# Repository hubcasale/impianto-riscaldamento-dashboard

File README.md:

# Impianto riscaldamento dashboard

Due schede Lovelace per Home Assistant, pensate per un impianto con **boiler solare**, **puffer** e
**caldaia a pellet Micronova (Nobis Polygon)** letta dall'integrazione
[`aguaiot_hubcasale`](https://github.com/hubcasale/home_assistant_micronova_agua_iot_hubcasale):

| Scheda | Cosa fa |
|---|---|
| `impianto-overview-card` | Il boiler solare con temperatura alta e bassa, acqua in uscita e docce stimate; il puffer; la caldaia con fiamma piccola (accensione) o grande (in lavoro), stato, temperature, pressioni, contatori del giorno e le richieste del sistema di suggerimento. |
| `caldaia-schedule-card` | La programmazione settimanale della caldaia: 4 programmi con orari, giorni e set di temperatura, **vista settimanale a barre**, **avviso di sovrapposizione** e **preset** (feriale, weekend, vacanza…) con un tocco. |

Funzionano sia su tema chiaro che scuro (usano i colori del tema di Home Assistant) e si adattano al telefono.

> Gli screenshot vengono dal banco di prova (`dev/index.html`) con dati di esempio.
> Il lunedì P1 e P3 si sovrappongono apposta, per mostrare l'avviso.

## Puffer senza Internet

La temperatura del puffer arriva dal cloud Micronova e senza Internet diventa non disponibile. `sensor.puffer_temperatura_effettiva` (in `ha-packages/caldaia_integrazione_blocco.yaml`) usa la lettura della caldaia finché c'è; se manca da più di 5 minuti la ricava dalla sonda ESP32 in ingresso alla serpentina di integrazione con il modello `puffer = T_amb + (sonda − T_amb) / k` (k = 0,753 e T_amb = 19,7 °C, ricavati il 8/10/2026 da 747 letture a pompa in marcia: errore medio 0,8 °C). La sonda legge il puffer solo con la pompa in marcia: a pompa ferma il valore non è affidabile e la regola di blocco/forzatura **non interviene mai**. Sulla scheda il puffer compare con la scritta «stima sonda». Parametri regolabili: minuti di attesa, k e temperatura ambiente.

## Pannello solare sulla scheda

Sotto il puffer da 50 litri la scheda disegna la sagoma del pannello solare, collegata alla serpentina solare del boiler. Il colore segue la temperatura (come il boiler, poi più scuro oltre i 65 °C).
- **Temperatura mostrata:** la stima del collettore (`sensor.solare_termico_t_collettore_stimata`), ritarata sulle letture reali del display del regolatore e valida sia a pompa ferma sia in marcia. La temperatura **misurata** in ingresso alla serpentina (`sensor.solare_termico_solare_serpentina_ingresso`) è il fluido dopo i tubi, circa 6-7 °C sotto il collettore: compare sui tubi, e diventa il valore del pannello solo se la stima manca.
- **Sui tubi** compaiono le temperature in ingresso e in uscita della serpentina solare; nel disegno del CLESS le sonde dei pozzetti (b di destra = S. BOILER della caldaia, c di destra = generatore, b di sinistra = minima per il riscaldamento, sonde ESP32 `..._puffer_generatore` e `..._puffer_minima_riscaldamento`).
- **Massima prevista del giorno** e **massima già raggiunta oggi**: `ha-packages/solare_pannello.yaml`. Il modello usa la previsione oraria di `weather.casale` (nuvolosità, temperatura, umidità), la posizione del sole, l'inclinazione e l'orientamento dei collettori, il modello del collettore già in uso e, nelle prime ore, l'**irraggiamento misurato adesso** (rapporto fra irraggiamento sul piano e cielo sereno, con peso che scende in circa 2 ore). La massima prevista non scende mai sotto quella già raggiunta. È una stima del collettore a pompa ferma: con la pompa in marcia il fluido misurato resta più freddo.
- Entità nuove: `sensor.solare_pannello_temperatura`, `sensor.solare_pannello_massima_prevista`, `sensor.solare_pannello_massima_oggi`, `sensor.solare_previsione_oraria`. Il fattore `input_number.solare_pannello_fattore_sereno` (1,00) calibra l'irraggiamento a cielo sereno.
- **Telefono:** sotto il boiler compare una fascia con il puffer e il pannello, con le scritte più grandi (le temperature in ingresso e in uscita delle serpentine sono indicate con le frecce → e ←). Sulla scheda larga i tubi riportano solo le temperature; la tessera «Solare» a sinistra mostra i kW.

## Stima del consumo di pellet

`ha-packages/caldaia_pellet.yaml` stima i chili di pellet bruciati e la scheda li mostra sotto i contatori di oggi (oggi, settimana, mese). È una **stima** da calibrare: la caldaia non comunica i chili. Il modello usa lo stato e la potenza reale:
- **WORK:** consumo interpolato fra i due valori del costruttore (1,63 kg/h al 30 %, 5,6 kg/h al 100 %) in base alla potenza reale (30 % al minimo, 100 % al massimo);
- **STAND BY e STOP:** consumo di mantenimento (0,2 kg/h, ipotesi);
- **ogni accensione** (ingresso in START): 200 g (ipotesi);
- ECO STOP, OFF e WAIT: nessun consumo.

Per tarare: dividi i chili di pellet realmente consumati in un periodo (sacchi aperti e finiti) per la stima dello stesso periodo e inserisci il risultato come fattore di taratura nelle preferenze (sezione «Consumo di pellet», ripiegata). Entità: `sensor.caldaia_pellet_oggi`, `_settimana`, `_mese` (si azzerano da sole), `sensor.caldaia_pellet_stimato_totale`, `sensor.caldaia_pellet_consumo_istantaneo` (kg/h).

Sui dati dal 2 al 6 ottobre 2026 il modello dà circa 2-6 kg al giorno, con poche ore in lavoro e molte accensioni.

## Preferenze dalla scheda dell'impianto

Il pulsante a forma di ingranaggio in alto a destra sulla scheda dell'impianto apre le preferenze, divise in **blocchi per funzione**: *Caldaia a pellet* (temperatura dell'acqua e set boiler), *Accumulo CLESS* e *Gestione dall'accumulo*, *Spegnimento se nessuno è in casa*, *Termostato ambiente* (si apre la finestra dell'integrazione `termostato_riscaldamento`, se è installata) e, sotto «Avanzate», *Consumo di pellet (stima)* e *Misura delle pompe*. Toccando un blocco si aprono le sue impostazioni; la **«i»** accanto a un blocco o a una voce apre una spiegazione con cosa fa, quando serve e, dove c'è, il valore consigliato (niente suggerimenti al passaggio del mouse: pensato per il tablet). Ogni modifica è attiva subito e resta anche dopo un riavvio. Le impostazioni i cui helper non esistono (pacchetto non installato) non compaiono. Per nascondere il pulsante: `settings: false` nella configurazione della scheda.

## Installazione

### HACS (repository personalizzato)

1. HACS → menu a tre punti → **Repository personalizzati** → incolla
   `https://github.com/hubcasale/impianto-riscaldamento-dashboard`, categoria **Dashboard**.
2. Installa **Impianto riscaldamento dashboard**.
3. Aggiungi le schede a una dashboard (vedi `examples/dashboard.yaml`).

### A mano

1. Copia `dist/impianto-riscaldamento-dashboard.js` in `<config>/www/`.
2. Impostazioni → Dashboard → Risorse → aggiungi `/local/impianto-riscaldamento-dashboard.js` come **Modulo JavaScript**.
3. Ricarica la dashboard.

## `impianto-overview-card`

```yaml
type: custom:impianto-overview-card
title: Impianto acqua calda      # facoltativo
```

Senza altro usa questi nomi di entità (cambiali in `entities:` se i tuoi sono diversi):

| Chiave | Entità predefinita | Da dove viene |
|---|---|---|
| `boiler_top` | `sensor.boiler_solare_alto_stimato` | `ha-packages/boiler_solare.yaml` |
| `boiler_bottom` | `sensor.boiler_solare_basso_stimato` | idem |
| `outlet` | *(assente: si usa la sonda alta)* | temperatura dell'acqua in uscita, se la misuri |
| `cless_mode` | `input_boolean.impianto_modo_cless` | pacchetto `impianto_cless` (vedi «Modo CLESS») |
| `solar_power`, `collector_temp` | `sensor.solare_termico_potenza`, `sensor.solare_termico_t_collettore_stimata` | pacchetto solare termico |
| `puffer`, `stove_state`, `stove_water`, `smoke`, `flame`, `power`, `water_pressure`, `brazier_pressure`, `extractor`, `pump`, `alarm` | `sensor.casale_*` | integrazione `aguaiot_hubcasale` |
| `set_boiler`, `set_water` | `number.casale_setpoint_boiler`, `climate.casale_acqua` (attributo `temperature`) | integrazione |
| `pellet_reserve`, `pellet_empty`, `pellet_open` | `binary_sensor.casale_riserva_legna` (riserva: sta per finire), `binary_sensor.casale_pellet_empty` (vuoto), `binary_sensor.casale_pellet_hopper_open` (serbatoio aperto) | integrazione `aguaiot_hubcasale` v1.2.7-hubcasale.4 (gli ultimi due) |
| `integration_pump`, `collector_pump` | `binary_sensor.caldaia_pompa_integrazione_attiva`, `binary_sensor.caldaia_pompa_collettore_attiva` | `ha-packages/caldaia_pompe_centralina.yaml` (dalla potenza della centralina solare) |
| `integration_power`, `collector_power` | `sensor.garage_bs_pompa_integrazione_potenza` (Shelly 1PM), `sensor.garage_centralina_solare_pompe_potenza` (Shelly EM Mini sull'alimentazione dell'Elios) | i watt accanto alle pompe in marcia |
| `integration_call`, `integration_block_enabled`, `integration_block_wanted` | `binary_sensor.garage_bs_pompa_integrazione_ingresso_0`, `input_boolean.caldaia_integrazione_blocco_attivo`, `binary_sensor.caldaia_integrazione_inutile` | `ha-packages/caldaia_integrazione_blocco.yaml`: la scritta arancione «integrazione bloccata» compare quando il blocco è acceso, la regola lo chiede e l'Elios chiama la pompa |
| `starts_today`, `starts_yesterday`, `standby_today`, `work_hours_today` | `sensor.caldaia_*` | `ha-packages/caldaia_suggerimento.yaml` |
| `request_acs`, `request_heating`, `consent` | `binary_sensor.caldaia_richiesta_acs` … | idem |

Il numero di **docce** si calcola con un modello a due zone: la parte alta del serbatoio (quota `top_share`)
è alla temperatura della sonda alta, il resto a quella della sonda bassa; ogni zona sopra la temperatura
della doccia dà `litri × (T − T_rete) / (T_doccia − T_rete)`. Parametri (numero o id di entità):

```yaml
model:
  volume: 190          # litri utili (predefinito: input_number.boiler_solare_volume)
  top_share: 50        # % di volume della zona alta (predefinito: input_number.boiler_solare_peso_alto)
  mains_temp: 15       # °C acqua di rete (predefinito: input_number.boiler_solare_t_rete)
  shower_volume: 40    # litri per doccia
  shower_temp: 38      # °C della doccia
```

Sotto i 560 px di larghezza il disegno del boiler perde il puffer (resta nelle tessere) per restare leggibile.

**Termostato ambiente sotto la caldaia** (`thermostat: false | { entry_id, title }`): se è installata l'integrazione [termostato-riscaldamento](https://github.com/hubcasale/termostato-riscaldamento) la scheda mostra sotto la caldaia il quadrante con la temperatura, l'obiettivo con + e − e le modalità Programma, Manuale, Timer e Spento. Senza l'integrazione non compare niente. Per nasconderlo: `thermostat: false`. La colonna della caldaia mostra quattro valori (puffer, set boiler, set acqua, potenza), i contatori di oggi e le tre richieste (l'interruttore «Evita partenze inutili» sta nelle preferenze, blocco «Salvaguardia accensioni»); fumi, fiamma, pressioni, estrattore, circolatore, accensioni di ieri, allarme e stima del pellet stanno nella finestra **«Altri dati»**; un allarme in corso resta sempre visibile sulla scheda.

**Layout «split» e pellet nel serbatoio (prova)** (`layout: split`, predefinito `classic`): su schermo largo (oltre 1150 px) boiler, caldaia e stufa a pellet stanno in **tre schede alte uguali**, con lo stesso sfondo, bordo e angoli, e il **termostato** occupa la striscia in basso su tre colonne (quadrante | obiettivo e modalita' | stato, calendario e preferenze). Il boiler e' corto (un solo giro per serpentina). Con `stufa: true` e la scheda `stufa-pellet-card` caricata la stufa e' la scheda completa incorporata (senza la scheda resta la sintesi con il pulsante «Scheda completa»). Sotto i 1150 px le schede si impilano (boiler, caldaia, stufa, termostato). La figura della caldaia ha **a sinistra l'armadio del serbatoio** con il disegno del serbatoio (stessa forma di quello vero: parte alta, trapezio e punta) riempito fino ai chili rimasti, con i chili, i giorni di autonomia e lo stato del pellet nella parte libera a destra del serbatoio, e **a destra il corpo della caldaia** con la finestra della fiamma, in alto l'ultimo cambio di stato e in basso lo stato (OFF, WORK, ECO STOP...) e la temperatura dell'acqua. Toccando il serbatoio si apre la finestra **«Pellet nel serbatoio»**: con **«Ho versato dei sacchi»** si aggiungono i sacchi (passo di mezzo sacco) e con **«Ho misurato il livello»** si scrive la quota dalla sommita' in cm. Con **«Ho versato dei sacchi e misurato la quota»** si danno insieme i sacchi, la quota di prima (facoltativa) e quella dopo: imposta il livello dalla quota dopo e mostra l'aumento in chili accanto a sacchi x peso, con la densita' che la geometria richiederebbe (solo se la quota di prima e' misurata), per controllare le misure del serbatoio. Il conteggio e' un riferimento (chili e totale stimato di quel momento) meno il consumo stimato da allora: serve il pacchetto `ha-packages/caldaia_pellet_serbatoio.yaml` (helper `caldaia_pellet_kg_riferimento`, `caldaia_pellet_totale_riferimento`, `caldaia_pellet_sacco_kg`; la prima volta si parte dal livello misurato). Il serbatoio tiene 8 sacchi da 15 kg (120 kg), 2,0 kg per cm nella parte alta; la forma e la tabella sono in `src/hopper-logic.ts`.

**Grafici del pellet** (pulsante «Grafici» in alto a destra del serbatoio): finestra con il periodo a scelta (24 ore, 3, 7, 14, 30 o 90 giorni), le caselle riassuntive (rimasti adesso, consumo medio, consumati e caricati nel periodo, quando finisce), il grafico dei **chili rimasti** con i **caricamenti** (freccia verde, «+15 kg») e le **letture del livello** (punto blu, con lo **scarto** rispetto alla stima in arancione) che si possono accendere e spegnere, il **consumo stimato per giorno** (per ora nel periodo di 24 ore) con la media e, sotto, l'elenco di caricamenti e letture con la **taratura** suggerita per il fattore (consumo reale / stimato). Toccando il grafico si legge il valore in quel momento. I caricamenti e le letture non sono registrati a parte: si riconoscono dai salti del conteggio (il rimasto cala esattamente quanto cresce il totale stimato, quello che non quadra è un evento; un salto vicino a un multiplo di mezzo sacco, o che riempie il serbatoio, è un caricamento), quindi appaiono fin dove arriva lo storico di Home Assistant (di solito 10 giorni); prima si vedono un andamento approssimato e il consumo dalle statistiche a lungo termine. Servono i sensori `sensor.caldaia_pellet_serbatoio` e `sensor.caldaia_pellet_stimato_totale` (pacchetti `caldaia_pellet_serbatoio.yaml` e `caldaia_pellet.yaml`).

**Cosa mostrare (una sola scheda per tutto l'impianto)**: nelle preferenze, blocco **«Pagina → Cosa mostrare»**, quattro interruttori accendono o spengono le sezioni **Boiler solare**, **Caldaia a pellet**, **Stufa a pellet** e **Termostato ambiente**: puoi vederne una sola o tutte. La scelta è **per utente** e resta salvata in Home Assistant (`frontend/set_user_data`, chiave `impianto_riscaldamento_sezioni`), quindi la ritrovi su tutti i tuoi dispositivi; l'ultima sezione rimasta non si può spegnere. Le colonne si adattano alle schede visibili (nel layout classic il boiler lascia tutta la larghezza alle altre). Se la caldaia è nascosta, l'ingranaggio delle preferenze passa in una barra in alto a destra. Gli interruttori compaiono solo per le sezioni disponibili (la stufa serve `stufa: true`, il termostato non dev'essere `thermostat: false`). Per cambiare la scelta di partenza (chi non l'ha mai fatta) c'è `show: [boiler, caldaia, stufa, termostato]` nella configurazione YAML.

**Colore della scheda** (`color`, dall'editor: «Colore della scheda»): lo sfondo della scheda prende una tinta del colore scelto e il bordo lo segue, come un blocco colorato della plancia; i pannelli interni (boiler, caldaia, stufa, termostato, stanze) restano come li disegna il tema. Vale un nome della tavolozza di Home Assistant (`deep-orange`, `blue`, `amber`…) oppure, nello YAML, un colore CSS (`#ff5722`). Senza `color` la scheda resta com'è.

**Preferenze dell'impianto**: l'ingranaggio sta nel titolo della scheda della caldaia, accanto a «Programma» (`settings: false` lo toglie).

**Programmazione della caldaia** (`schedule: false | { prefix, master, status, presets }`, predefinito attivo): nel titolo della scheda della Polygon c'è il pulsante **«Programma»**, che apre in un popup la scheda della programmazione settimanale (`caldaia-schedule-card`) senza passare da altri pop-up o pulsanti della dashboard. Un oggetto passa le opzioni alla scheda della programmazione; `schedule: false` toglie il pulsante.

**Sintesi della stufa a pellet (prova)** (`stufa: true | { entry_id, title }`, predefinito spenta): se è installata l'integrazione [stufa-pellet-monitor](https://github.com/hubcasale/stufa-pellet-monitor), a destra della scheda della caldaia compare una sintesi della stufa: stato e da quanto dura, modo (programma, manuale, timer), potenza, il pulsante di **accensione manuale** dell'interruttore (apre una finestra di conferma) e **«Scheda completa»**, che apre in un popup la scheda `stufa-pellet-card`, aggiornata in tempo reale. Il termostato resta intero sotto. Quando la scheda è più stretta di 1150 px (portatili piccoli, tablet in verticale, telefoni) la sintesi va sotto la caldaia, a tutta larghezza. Senza l'integrazione, o senza `stufa`, non cambia niente.

## `caldaia-schedule-card`

```yaml
type: custom:caldaia-schedule-card
title: Programmazione caldaia     # facoltativo
prefix: casale                    # prefisso delle entità dell'integrazione
hide: [weekly]                    # facoltativo: nasconde "weekly" e/o "presets"
```

Usa le entità create dall'integrazione, per ogni programma N da 1 a 4:
`time.casale_crono_pN_accensione`, `time.casale_crono_pN_spegnimento`,
`number.casale_crono_pN_setpoint_boiler`, `number.casale_crono_pN_setpoint_acqua`,
`switch.casale_crono_pN_<giorno>` (lunedi … domenica) e l'interruttore generale
`switch.casale_cronotermostato_settimanale`.

- **Orari a passi di 10 minuti** (come la caldaia). Spegnimento `00:00` = fino a mezzanotte.
- **Sovrapposizioni**: se due programmi attivi si incrociano nello stesso giorno compare un avviso in alto e la
  fascia è tratteggiata in rosso nella vista settimanale. Fasce che si toccano soltanto non contano; un programma
  che scavalca la mezzanotte occupa anche il giorno dopo.
- **Vista settimanale**: una riga per giorno, con la linea dell'ora attuale.
- Le modifiche sono scritte subito. I campi si attenuano finché la caldaia non conferma (passa dal cloud, può
  servire qualche minuto).

### Preset

Quattro preset predefiniti: *Settimana tipo*, *Feriale*, *Weekend*, *Vacanza*. Toccando un preset la scheda
mostra **che cosa cambierebbe** e chiede conferma; applica solo le differenze. Si possono sostituire:

```yaml
presets:
  - name: Mattina e sera
    icon: mdi:weather-sunset
    description: Dalle 5:30 alle 8 e dalle 17 alle 22:30
    crono: true                 # true/false = attiva/disattiva il cronotermostato; assente = non toccarlo
    programs:
      "1": { on: "05:30", off: "08:00", days: [lun, mar, mer, gio, ven, sab, dom], set_boiler: 45, set_water: 65 }
      "2": { on: "17:00", off: "22:30", days: [lun, mar, mer, gio, ven, sab, dom] }
      "3": null                 # null (o days: []) = programma disattivato
      # "4" non elencato = resta com'è
```

I giorni si scrivono in italiano o inglese, corti o lunghi (`lun`, `mon`, `lunedì`…).

#### Salvare i propri preset

Il pulsante **Salva…** accanto ai preset salva la programmazione attuale (orari, giorni e set di temperatura dei quattro programmi, più lo stato del cronotermostato): scegli quale preset sostituire (anche quelli predefiniti) oppure dai un nome a un preset nuovo. Prima di salvare vedi le righe che verranno memorizzate. I preset salvati compaiono insieme agli altri; per quelli predefiniti sostituiti c'è «Ripristina», per quelli nuovi «Elimina». Si salvano nei dati utente di Home Assistant (`frontend/set_user_data`, chiave `impianto_riscaldamento_presets`), quindi restano dopo gli aggiornamenti e valgono su tutti i dispositivi dello stesso utente. Con `presets:` nella configurazione si sostituiscono i predefiniti, e quelli salvati vengono sopra.

## Pacchetti di Home Assistant e ESPHome

Le schede leggono sensori che qui sono forniti come esempio:

- `ha-packages/boiler_solare.yaml`: temperature stimate alta e bassa (con una correzione provvisoria di accoppiamento rispetto alla centralina
  solare, vedi `docs/MEMORIA.md`), media, stratificazione, energia accumulata e acqua calda equivalente.
- `ha-packages/caldaia_suggerimento.yaml`: suggerimento informativo di accendere o no la caldaia, contatori di
  accensioni e ore in lavoro. **Non comanda niente.**
- `ha-packages/caldaia_tempo_acqua.yaml`: misura quanti minuti servono, dopo un'accensione a freddo, per portare il boiler solare
  alla temperatura d'uso e ne fa la media (ultimi 10 campioni, correggibili a mano).
- `ha-packages/caldaia_pompe_centralina.yaml`: dalla potenza totale della centralina solare (`sensor.garage_centralina_solare_pompe_potenza`) ricava quale pompa gira (ferme sotto 15 W, solo collettore fino a 42 W, solo integrazione tra 42 e 65 W, entrambe da 65 W; soglie modificabili, tarate sulle misure del 5/10/2026) e le ore di funzionamento di oggi.
- `ha-packages/caldaia_accensione_rapida.yaml`: pulsante **Avvia caldaia** per quando serve acqua calda e la Polygon è spenta,
  con spegnimento automatico (vedi sotto) e la stima `sensor.caldaia_acqua_pronta_tra`.
- `esphome/solare-termico.yaml`: ESP32 con ADS1115 e sonde NTC 10k B3950 (serpentine) e due sonde sul boiler.

## Stanze: temperatura e umidità

Accanto al termostato la scheda dell'impianto mostra la scheda **Stanze**: una colonna per ogni stanza (altezza e colore secondo la temperatura, umidità sotto), la linea tratteggiata dell'obiettivo del termostato e, in alto, tre chip: la stanza più calda, la più fredda e quelle con umidità da 70 % in su. Nel layout `split` (tablet, scheda larga almeno 1150 px) il termostato occupa metà riga e le stanze l'altra metà; sotto quella larghezza stanno una sotto l'altra. Un tocco su una colonna apre i **Grafici** sul gruppo *Stanze*, con temperatura (scala a sinistra) e umidità (a destra) di quella stanza; gli altri sensori si accendono dai pulsanti sopra il grafico.

- Colori della temperatura: da 22 °C in su arancione, sotto 19 °C azzurro, in mezzo verde. Umidità: da 60 % gialla, da 70 % rossa, sotto 40 % azzurra.
- Le stanze di partenza e i loro sensori MQTT: Soggiorno, Cucina, Camera matrimoniale, Camera Matilde, Camera Camilla, Bagno Blu (`sensor.sensore_<stanza>_temperature` e `..._humidity`) e Bagno Verde, che resta un segnaposto finché non esiste il suo sensore. La scheda compare se almeno uno di questi sensori esiste.
- Con la configurazione YAML si cambiano le stanze, il titolo o il termostato dell'obiettivo; `rooms: false` la nasconde:

```yaml
type: custom:impianto-overview-card
layout: split
rooms:
  title: Stanze
  target_entity: climate.termostato
  rooms:
    - { id: studio, name: Studio, short: Studio, temperature: sensor.studio_temperatura, humidity: sensor.studio_umidita }
```

La scheda si può usare anche da sola: `type: custom:impianto-rooms-card` (opzioni `title`, `rooms`, `target_entity`).

## Modo CLESS

Con l'accumulo REQ.A CLESS al posto del boiler solare da 200 L e del puffer da 50 L si accende `input_boolean.impianto_modo_cless` (pacchetto `ha-packages/impianto_cless.yaml`). Da acceso:

- la scheda disegna l'accumulo senza puffer, senza serpentina e pompa di integrazione e senza il pulsante di accensione rapida; al posto dell'«Acqua pronta in» mostra il setpoint della sonda S. BOILER, e la finestra «Stato» parla della sonda S. BOILER invece del puffer;
- il modello del serbatoio passa a 510 L (zona alta circa il 45 %), le correzioni delle sonde ESP32 vanno a 0 (da rifare confrontando la sonda alta con la S. BOILER) e le docce si contano sopra i 47 °C (la serpentina sanitaria non raffredda l'accumulo oltre quella soglia): con la cima a 65 °C sono circa 4, non 12 come col conto da boiler a serbatoio;
- la salvaguardia delle partenze inutili, il blocco della pompa di integrazione e la misura del tempo per l'acqua pronta si fermano (la caldaia resta sempre accesa per l'acqua calda);
- se la caldaia resta spenta più di 20 minuti (regolabile) senza programma settimanale e con qualcuno in casa arriva un avviso sul telefono; non viene riaccesa da sola.
- la **gestione dall'accumulo** (pacchetto `ha-packages/caldaia_accumulo.yaml`, interruttore `input_boolean.caldaia_accumulo_attivo`) decide le ripartenze dalla sonda S. BOILER invece che dall'acqua della caldaia: se la caldaia riparte da sola da ECO STOP o STAND BY con S. BOILER a 55 °C o più (`input_number.caldaia_accumulo_t_spegni`) e nessuno chiede calore, la partenza si annulla in fase di accensione (anche se il termostato chiede riscaldamento: i radiatori sono serviti dall'accumulo); spenta così, si riaccende quando S. BOILER scende sotto 53 °C (`..._t_accendi`) o quando la caldaia chiede riscaldamento con l'accumulo sotto la soglia di spegnimento. Non tocca le partenze da OFF (a mano, app, accensione rapida), l'accensione rapida in corso e gli allarmi; in questo caso l'avviso di caldaia spenta non scatta.

Nelle Preferenze, col modo CLESS acceso, il blocco **Gestione dall'accumulo** (interruttore e le due soglie) è accanto a quello dell'accumulo; il campo del setpoint della caldaia diventa «Set boiler (sonda S. BOILER)» con una nota sull'isteresi dell'acqua. I blocchi del vecchio impianto (salvaguardia delle accensioni, richiesta di acqua calda, pompa di integrazione) sono stati tolti dalle preferenze: le loro helper e i pacchetti restano in Home Assistant, ma non si comandano più da qui.

L'interruttore, le correzioni delle due sonde, la soglia delle docce e l'avviso di caldaia spenta stanno nelle **Preferenze impianto → Accumulo CLESS** (l'interruttore è nell'intestazione del blocco). Da spento torna tutto com'era (200 L, 50 %, correzioni +4 e +3 °C). Senza il pacchetto, o con il modo spento, la scheda non cambia.

## Pulsante «Stato»

Sotto il pulsante di accensione rapida, sul lato sinistro dello schema, c'è il pulsante **Stato** (con una «i»). Apre una finestra con poche righe che dicono che cosa sta succedendo: la caldaia (in lavoro, in ECO STOP con la temperatura del puffer a cui riparte, in accensione, spenta e perché: vacanza, fuori fascia, salvaguardia, assenza), la pompa di integrazione (accesa o ferma e il motivo), il solare, chi è in casa con il conto alla rovescia dello spegnimento per assenza, il tempo per l'acqua calda e gli avvisi di allarme o pellet. La finestra segue gli stati in tempo reale. Si nasconde con `summary: false`. La logica è in `src/summary-logic.ts`.

## Pulsante «Grafici»

Sotto «Stato» c'è il pulsante **Grafici**: apre una finestra con lo storico (letto dal recorder di Home Assistant, nessuna libreria esterna) di quattro gruppi di valori: *Temperature* (puffer, boiler alto e basso, acqua della caldaia, collettore), *Caldaia* (acqua, puffer, fumi e potenza), *Pompa di integrazione* (puffer, boiler, serpentina e potenza della pompa) *AllSky* (irraggiamento orizzontale della stazione, originale e corretto, stimato dalla foto, e copertura nuvolosa), *Irraggiamento* (sul piano dei collettori: stazione, previsione di Open-Meteo, osservato dal satellite, con la nuvolosità prevista a destra; il satellite è spostato indietro di 2 ore perché pubblica in ritardo) e *Solare* (collettore, serpentine, potenza), più un *Confronto libero* con tutte le serie.

Col modo CLESS acceso le legende usano per tutte le sonde dell'accumulo la stessa forma dei sensori in Home Assistant (*Puffer alto (S3)*, *Puffer basso (S2)*, *Puffer S. BOILER (caldaia)*, *Puffer generatore (c)*, *Puffer minima riscaldamento (b)*) e il gruppo *Pompa di integrazione* è sostituito dal gruppo *Puffer* con le cinque sonde.

- **Periodo:** 6 ore, 24 ore, 3 o 7 giorni.
- **Sovrapporre:** ogni serie si accende e si spegne dai tasti sopra il grafico; «Confronta con il periodo prima» disegna in tratteggio lo stesso intervallo precedente; «Confronta le forme (0–100 %)» riporta ogni serie al proprio minimo-massimo per sovrapporre grandezze diverse (nel confronto libero è sempre attivo).
- **Leggere i valori:** passando il mouse o il dito sul grafico compare la linea del cursore con i valori di tutte le serie (e quelli del periodo prima); sotto, la tabella con valore al cursore (o attuale), minimo, media e massimo.
- **Stato della caldaia:** una fascia colorata sotto il grafico (in lavoro, accensione, ECO STOP, spenta) per capire perché le temperature cambiano.

Si nasconde con `charts: false`. La logica (campionamento, scale, assi) è in `src/charts-logic.ts`, il disegno in `src/charts-dialog.ts`.

## AllSky: copertura nuvolosa e irraggiamento dalla foto

`ha-packages/solare_allsky.yaml` e la cartella `allsky/` (`allsky_clouds.py`, `allsky_config.json`, `obst_mask.png`, `solpos.py`, da copiare in `/config/allsky/`). Ogni 3 minuti di giorno lo script scarica l'ultima immagine dal web server dell'allsky (`image_url` in `allsky_config.json`), esclude con una maschera gli ostacoli fissi (edifici, alberi, antenne), classifica il cielo in **sereno / velato / coperto** dal colore e guarda il **disco del sole e l'alone** intorno, da cui stima la trasmissione dell'irraggiamento rispetto al cielo sereno. Gira come processo separato (`command_line`, con le coordinate di `zone.home`) e non da' nessun valore di notte, con il sole sotto gli 8 gradi o con la foto vecchia di piu' di 15 minuti.

Sensori: `sensor.allsky_analisi` (stato e attributi), `sensor.allsky_copertura_equivalente` (%), `binary_sensor.allsky_sole_libero`, `sensor.allsky_irraggiamento_stimato` (W/m², orizzontale) e `sensor.irraggiamento_stazione_corretto`.

**Taratura (12/10/2026):** geometria dell'obiettivo (centro 999, 750, raggio 665 px su 2000 px, rotazione 14°) verificata sul sole in foto serene; sulle 399 foto di 8 giorni il modello spiega il 62 % della variabilita' del rapporto irraggiamento reale / cielo sereno (convalida un-giorno-alla-volta, errore tipico 0,11). La stazione (BH1750 lux / 120) legge circa il 54 % dell'irraggiamento osservato dal satellite: `input_number.solare_fattore_stazione` (1,6) la porta a W/m² realistici nei sensori «corretto» e «stimato»; il sensore originale, che alimenta il modello del collettore e l'irrigazione, non e' stato toccato.

## Orizzonte reale: dove il terreno nasconde il sole

`ha-packages/solare_orizzonte.yaml` e `allsky/horizon_profile.json`. Dalla maschera degli ostacoli dell'allsky si ricava, ogni 3 gradi di azimut, l'elevazione minima con cielo libero (nord, est e ovest-nord-ovest quasi piatti; nel quadrante sud-ovest, 210-250 gradi, il terreno sale a 7-11 gradi). Con il percorso del sole risulta che in autunno e in inverno il sole sparisce 25-60 minuti prima del tramonto astronomico (14/10: 18:20 contro 17:55; 15/02: 17:30 contro 16:30), proprio quando il collettore a ovest rende di piu'.

Sensori: `sensor.sole_orizzonte_profilo` (attributo `profilo`), `sensor.sole_elevazione_orizzonte` (terreno nella direzione del sole) e `binary_sensor.sole_sopra_l_orizzonte`. Interruttore `input_boolean.solare_orizzonte_attivo`: acceso, la **massima prevista del pannello** (`solare_pannello.yaml`) toglie il contributo diretto nelle ore in cui il sole e' dietro il terreno (resta il diffuso) e compaiono `sensor.open_meteo_energia_prevista_oggi_con_orizzonte` e `..._domani_con_orizzonte` (kWh/m²), che sottraggono alla previsione di Open-Meteo la quota diretta (direct/shortwave) di quelle ore. A meta' ottobre l'effetto e' circa -4 % sull'energia del giorno; sulla temperatura massima non cambia perche' il massimo e' a mezzogiorno.

Nella finestra **Stato** la scheda spiega anche il sole: dietro le colline, libero con cielo molto nuvoloso (il collettore lavora a luce diretta anche se la temperatura esterna cala), libero con poche nuvole, coperto (solo luce diffusa) o coperto da una sola nuvola con cielo quasi sereno.

## Spegnimento con nessuno in casa

`ha-packages/caldaia_assenza.yaml`. La presenza viene dai quattro iPhone di iCloud3 (`device_tracker.iphone_camilla/corrado/matilde/roberta`) **e** dal Wi-Fi: nessun iPhone deve risultare connesso a `CASALE2G` (i `device_tracker` del router hanno l'attributo `ssid`). Se una delle due fonti non è disponibile non si considera nessuno fuori. Dopo 60 minuti di assenza (regolabili) la Polygon accesa viene fermata, tranne con termostato che chiede calore, modalità ospiti, accensione rapida, gelo (meno di 5 °C fuori) o caldaia già spenta o in allarme. Al rientro si riaccende solo se un programma è attivo in quel momento. Interruttore: `input_boolean.caldaia_assenza_attiva`; ospiti: `input_boolean.caldaia_assenza_ospiti`.

## Accensione rapida

Sulla scheda panoramica, sotto la sonda alta, ci sono i minuti stimati per avere l'acqua a temperatura d'uso
(0 se lo è già) e il pulsante. Il pulsante apre una **finestra di conferma** («Avviare la caldaia?», con il tempo stimato per l'acqua calda; il focus parte su «Annulla») e il comando parte solo se premi «Avvia»; funziona solo se:
la Polygon è spenta (OFF), non c'è allarme, la sonda alta stimata è sotto la temperatura d'uso (45 °C), il puffer non è
già sopra la soglia (50 °C) e non si è superato il limite di accensioni rapide del giorno (2).

Quando la caldaia ha lavorato e va in **ECO STOP**, viene spenta per non farla riaccendere, a meno che altro la debba
tenere accesa: il termostato dei radiatori che chiama calore o un programma della Polygon attivo in quel momento.
Si spegne quando il puffer scende sotto la soglia (e l'acqua è a temperatura) oppure dopo la durata massima (2 ore).
Lo spegnimento avviene solo in ECO STOP, mai durante START o WORK. Un tocco su **Annulla** interrompe la richiesta.

## Documentazione

- [`docs/MEMORIA.md`](docs/MEMORIA.md): come funziona il sistema, scelte fatte, entità, cose da verificare.
- [`docs/schema-cablaggio.png`](docs/schema-cablaggio.png): schema dei collegamenti dello Shelly 1PM sulla pompa di integrazione (Elios OUT2 come segnale).
- [`docs/funzionamento.png`](docs/funzionamento.png): diagramma di flusso (accensione rapida, spegnimento, salvaguardia, misura dei tempi).

## Sviluppo

```bash
npm install
npm test            # prove della logica (programmazione, sovrapposizioni, preset, docce, pulsante)
python3 test-ha/test_templates.py   # prove offline dei template Home Assistant dell'accensione rapida
npm run typecheck
npm run build       # dist/impianto-riscaldamento-dashboard.js (da pubblicare nel repository)
npm run build:dev   # dev/bundle.js, poi apri dev/index.html nel browser
```

`dev/index.html` è un banco di prova con una finta Home Assistant (stati e servizi simulati):
`?tema=chiaro|scuro`, `?stato=WORK|START|ECO STOP|STAND BY`, `?larghezza=380`.

## Cose da sapere / limiti

- La scrittura dei **giorni** e degli **orari** passa dal cloud Micronova: va provata sulla propria caldaia
  (conviene su un programma libero, con il cronotermostato spento).
- La stima delle **docce** e le temperature "stimate" dipendono dalla taratura delle sonde.
- Niente editor visivo per ora: la configurazione è in YAML.

## Licenza

MIT

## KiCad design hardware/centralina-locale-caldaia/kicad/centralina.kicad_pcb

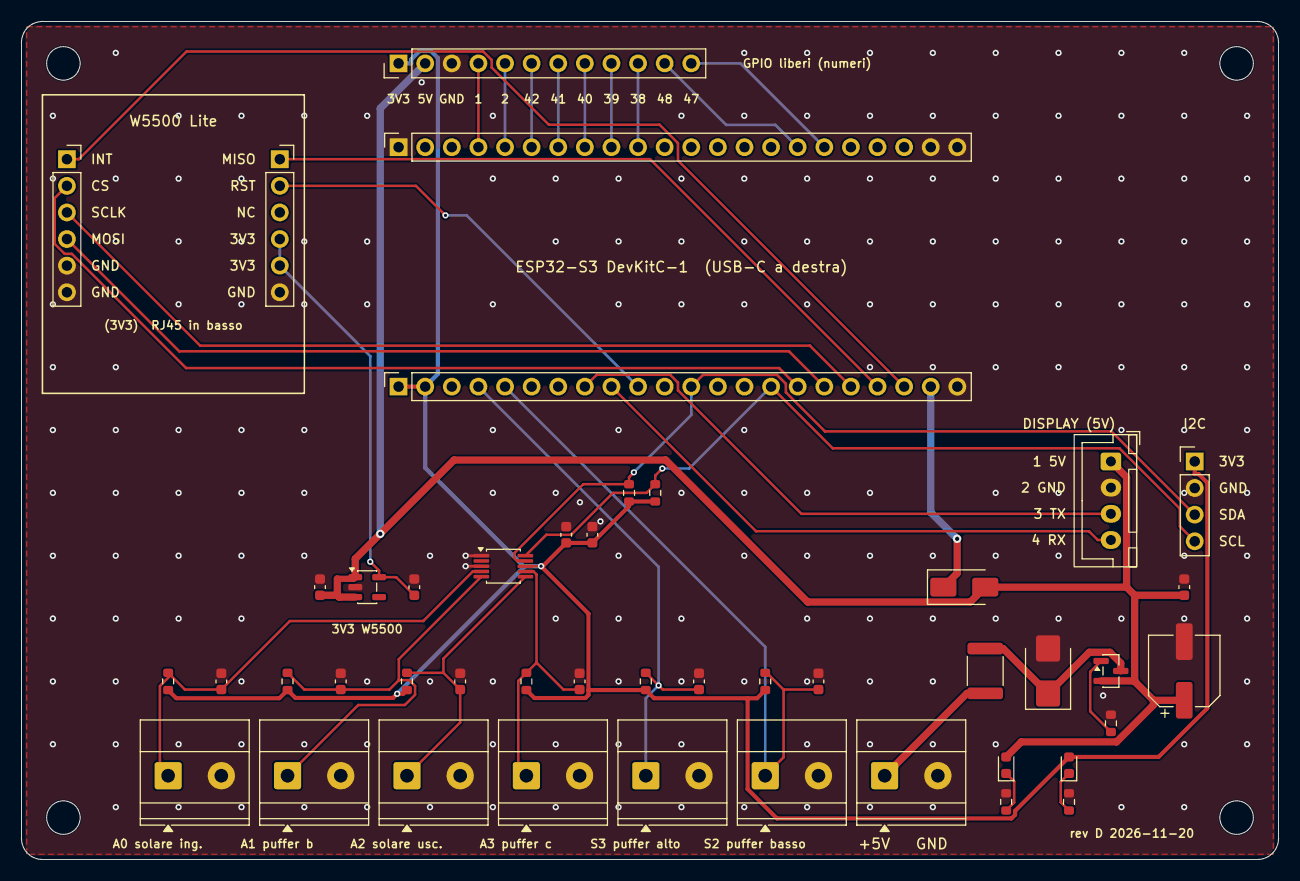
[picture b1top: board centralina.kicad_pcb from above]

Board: 2 copper layers, 120.0 x 80.0 mm, 49 parts (0 on the bottom side), 35 nets.

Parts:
C10: 100uF 10V; CP_Elec_6.3x5.4
C11, C20, C30, C31, C32, C33, C34, C35: 100n; C_0603_1608Metric
C21, C40, C41: 10u; C_0603_1608Metric
D1: SMBJ5.0A; D_SMB
D2: SS14; D_SMA
F1: PTC 1,5A; Fuse_1812_4532Metric
H1, H2, H3, H4: M3; MountingHole_3.2mm_M3
J1, J3: Presa femmina 1x22 2,54 mm; PinSocket_1x22_P2.54mm_Vertical
J10, J11, J12, J13, J14, J15, J16: Morsettiera 5,08 mm 2 poli; TerminalBlock_Phoenix_MKDS-1,5-2-5.08_1x02_P5.08mm_Horizont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
J20, J24: Presa femmina 1x6 2,54 mm; PinSocket_1x06_P2.54mm_Vertical
J21: JST XH 4 poli; JST_XH_B4B-XH-A_1x04_P2.50mm_Vertical
J22: Strip 1x4 2,54 mm; PinHeader_1x04_P2.54mm_Vertical
J23: Strip 1x12 2,54 mm; PinHeader_1x12_P2.54mm_Vertical
LED1: 5V; LED_0603_1608Metric
LED2: 3V3; LED_0603_1608Metric
Q1: AO3401A; SOT-23
R10: 10k; R_0603_1608Metric
R11, R12: 1k; R_0603_1608Metric
R20, R21: 4k7; R_0603_1608Metric
R30, R31, R32, R33, R34, R35: 10k 0.1%; R_0603_1608Metric
U1: ADS1115; MSOP-10_3x3mm_P0.5mm
U2: AP2112K-3.3; SOT-23-5

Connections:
+3V3: C20.1, C21.1, J1.1, J1.2, J22.1, J23.1, LED2.2, R20.1, R21.1, R30.1, R31.1, R32.1, R33.1, R34.1, R35.1, U1.8
+3V3_ETH: C41.1, J24.4, J24.5, U2.5
+5V: C10.1, C11.1, C40.1, D2.2, J21.1, J23.2, LED1.2, Q1.2, U2.1, U2.3
+5V_DK: D2.1, J1.21
ADC_S2: C35.1, J1.5, J16.1, R35.2
ADC_S3: C34.1, J1.4, J15.1, R34.2
DISP_RX: J1.9, J21.4
DISP_TX: J1.8, J21.3
ETH_CS: J1.16, J20.2
ETH_INT: J1.20, J20.1
ETH_MISO: J1.19, J24.1
ETH_MOSI: J1.17, J20.4
ETH_RST: J1.10, J24.2
ETH_SCLK: J1.18, J20.3
GND: C10.2, C11.2, C20.2, C21.2, C30.2, C31.2, C32.2, C33.2, C34.2, C35.2, C40.2, C41.2, D1.2, J1.22, J3.1, J3.21, J3.22, J10.2, J11.2, J12.2, J13.2, J14.2, J15.2, J16.2, J20.5, J20.6, J21.2, J22.2, J23.3, J24.6, R10.2, R11.2, R12.2, U1.1, U1.3, U2.2
GPIO1: J3.4, J23.4
GPIO2: J3.5, J23.5
GPIO38: J3.10, J23.10
GPIO39: J3.9, J23.9
GPIO40: J3.8, J23.8
GPIO41: J3.7, J23.7
GPIO42: J3.6, J23.6
GPIO47: J3.17, J23.12
GPIO48: J3.16, J23.11
I2C_SCL: J1.15, J22.4, R21.2, U1.10
I2C_SDA: J1.12, J22.3, R20.2, U1.9
LED3K: LED2.1, R12.1
LED5K: LED1.1, R11.1
N0: C30.1, J11.1, R30.2, U1.4
N1: C31.1, J12.1, R31.2, U1.5
N2: C32.1, J13.1, R32.2, U1.6
N3: C33.1, J14.1, R33.2, U1.7
Q1G: Q1.1, R10.1
VIN: F1.1, J10.1
VIN_F: D1.1, F1.2, Q1.3

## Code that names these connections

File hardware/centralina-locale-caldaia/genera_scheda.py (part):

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    1: "+3V3", 2: "+3V3", 4: "ADC_S3", 5: "ADC_S2", 8: "DISP_TX", 9: "DISP_RX", 12: "I2C_SDA", 15: "I2C_SCL",
    16: "ETH_CS", 17: "ETH_MOSI", 18: "ETH_SCLK", 19: "ETH_MISO", 20: "ETH_INT", 10: "ETH_RST", 21: "+5V_DK", 22: "GND",
}
J3 = {1: "GND", 21: "GND", 22: "GND", 4: "GPIO1", 5: "GPIO2", 6: "GPIO42", 7: "GPIO41", 8: "GPIO40", 9: "GPIO39", 10: "GPIO38",
      16: "GPIO48", 17: "GPIO47"}
place("J1", "Connector_PinSocket_2.54mm", "PinSocket_1x22_P2.54mm_Vertical", X0, Y_J1, rot=90, value="Presa femmina 1x22 2,54 mm", pads=J1)
place("J3", "Connector_PinSocket_2.54mm", "PinSocket_1x22_P2.54mm_Vertical", X0, Y_J3, rot=90, value="Presa femmina 1x22 2,54 mm", pads=J3)
text("ESP32-S3 DevKitC-1  (USB-C a destra)", X0 + 27, Y_J3 + ROW / 2, 1.0)
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      pads={"1": "+3V3", "2": "GND", "3": "I2C_SDA", "4": "I2C_SCL"})
pin_labels("J22", {"1": "3V3", "2": "GND", "3": "SDA", "4": "SCL"}, 2.2, 0.0, 0.9, "left")
text("I2C", 112, 38.4, 0.9)
hb = ["+3V3", "+5V", "GND", "GPIO1", "GPIO2", "GPIO42", "GPIO41", "GPIO40", "GPIO39", "GPIO38", "GPIO48", "GPIO47"]
place("J23", "Connector_PinHeader_2.54mm", "PinHeader_1x12_P2.54mm_Vertical", X0, 4, rot=90, value="Strip 1x12 2,54 mm",
      pads={str(i + 1): n for i, n in enumerate(hb)})
pin_labels("J23", {"1": "3V3", "2": "5V", "3": "GND", "4": "1", "5": "2", "6": "42", "7": "41", "8": "40", "9": "39", "10": "38", "11": "48", "12": "47"}, 0.0, 3.4, 0.8, "center")
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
